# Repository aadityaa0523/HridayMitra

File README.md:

# HridayMitra: early warning of worsening heart failure at home

> **Monitoring, not diagnosis.** Research prototype for the Transfinitte 2026 hackathon (hardware track, problem statement by Dare 2 Dream Ventures).
> All patient data in this repository is **synthetic** (plus public PhysioNet BIDMC ECG for heart rate). No human data was collected.

**In one line:** a 90-second daily check-in on the patient's own chair, an amulet, and an offline alert engine that warns the family **days before** a heart-failure hospital visit (up to **4 days** in our worked example, median 3), for a build cost of about **₹4,400**.

**Jump to:** [The problem](#the-problem-and-the-idea) · [How it works](#how-it-works) · [Results](#results) · [Quick start](#quick-start) · [Saathi phone app](#saathi-phone-app) · [Hardware and firmware](#hardware-and-firmware) · [Simulate it](#simulate-it-no-hardware) · [Reproduce](#reproduce-everything) · [Repository map](#repository-map) · [Documents](#documents) · [Troubleshooting](#troubleshooting) · [Honest limits](#honest-limits)

---

## The problem and the idea

Fluid builds up silently for days before a heart-failure admission. A daily weight rule catches about one event in three and floods families with false alarms. Elders will not wear sticky patches, and rural homes have power cuts, 2G and low literacy.

HridayMitra measures what a weight scale cannot (fluid in the legs and chest) in the way an elder will actually accept (sit down, hands on a bar), learns each person's *own* normal, and tells the family **why** it raised an alert, by SMS, with no internet.

| Part | What it is | What it measures |
|---|---|---|
| **Check-in set** | A weighing platform under the patient's own chair (4 load cells, 4 stainless foot plates) plus a hand sensor bar (4 hand strips, fingertip optical cradle, ✓ / ✗ / SOS buttons, speaker, status light). No chair modification; never on wheeled chairs. | Weight; 8-electrode bioimpedance spectroscopy at 5 / 20 / 50 kHz (legs, arms, both sides → chest fluid by segmental subtraction; water outside the cells from a Cole-model fit, which cancels foot position and skin temperature); pulse and SpO₂; sit-to-stand speed from the platform's force; 3 spoken yes/no questions |
| **Kavach amulet** | ESP32-C3 + accelerometer on a breakaway cord, no magnets | Night breathing, night sit-ups, activity, a weekly 6-minute walk test (it finds the best 6 minutes itself, no button), falls, SOS |
| **Offline alert engine** | Runs on the ESP32 | Personal baseline, green / amber / red, reasons in plain words |
| **Care loop** | SMS over 2G with retries | family 1 → family 2 (30 min) → ASHA worker (2 h) → PHC doctor (6 h) |
| **Saathi app** | Offline PWA, 10 Indian languages | Elder, family, ASHA and doctor views |

## How it works

```mermaid
flowchart LR
  A[Kavach amulet<br/>ESP32-C3 + MPU6050] -- BLE advertisement, no pairing --> S
  S[Check-in set<br/>ESP32 + load cells + 8-electrode impedance + finger sensor<br/>offline alert engine] -- light + voice --> E[Elder]
  S -- SMS over 2G --> C[Care loop<br/>family 1 → family 2 → ASHA → PHC doctor]
  S -- BLE or USB --> P[Saathi phone app]
  S -- USB, optional --> D[Laptop bridge → live dashboard]
```

**The alert engine** (`engine/alert_engine.py`): each person's baseline is the median/MAD of their own days t−35..t−7. Only the worsening direction is scored. Red needs **two independent witnesses** (for example weight and leg fluid), and bad-data guards ignore guests on the platform, a toe ring bridging two plates, lifted feet and noisy fingers. The same engine exists three times and is held identical by tests:

| Where | File | Checked by |
|---|---|---|
| Python (research, dashboard) | `engine/alert_engine.py` | reference |
| C++ on the ESP32 | `firmware/hridaymitra_stool/engine_core.h` | `tests/test_engine_parity.py`: 100% of 3,231 days |
| TypeScript in the app | `app/src/engine/` | `app/tests/engine.test.ts` against `docs/app/engine_test_vectors.json` (2,732 comparisons) |

**Hybrid engine** (`engine/hybrid.py`): rules propose, a 13-weight logistic model trained on dev only must agree before red. It runs on the laptop and in the benchmark; the stool itself runs rules v3.

## Results

Synthetic cohorts; thresholds tuned on training patients, frozen, then tested once.

| | Rules engine v3 | Hybrid (rules + ML) | Weight rule (SCALE-HF) |
|---|---|---|---|
| Sensitivity, held-out patients | **66%** | **86%** | 40% |
| Sensitivity, external 1,000-patient cohort | **72%** | **86%** | 31% |
| Specificity (held-out) | 98.7% | 97.9% | 97.6% |
| False alerts per patient-month (held-out / external) | **0.06 / 0.06** | 0.19 / 0.09 | 0.53 / 0.38 |
| Median lead time before the visit | 3 days | 3 days | 2 days |

Full tables with 95% ranges and an open scorer anyone can run: [`benchmark/LEADERBOARD.md`](benchmark/LEADERBOARD.md), [`benchmark/README.md`](benchmark/README.md).

- **Calibrated to real trials.** The published FAST and SCALE-HF 1 weight rules score on our external cohort 20% / 33% caught and 4.8 / 4.85 unexplained alerts per year, against the published 23% / 35% and 4.3 / 4.18.
- **Robust.** It beats the weight rule in all 52 assumption-sensitivity scenarios and 14 of 15 stress cases. In the 15th (10% guest days) the rule catches more but fires about 30× more false alerts.
- **Care loop.** In simulation 92% of red alerts get a clinical review before the hospital visit, versus 27% with a single SMS.
- **Circuit.** LTspice puts every path within 0.05% of the exact answer. A Monte Carlo of 100 stools built from 5% parts keeps 99% of readings within 2%, and it found a real design bug (bias resistors 1 MΩ → 10 MΩ).
- **Heart rate on real ECG.** All 15 PhysioNet BIDMC CHF records: median error 0.15 bpm, 13 of 15 within 0.5 bpm. It fails on chf12, a very noisy recording.
- **Cost.** Parts list ₹3,917 (low) to ₹4,890 (plan price). Monte Carlo of price noise: median ₹4,402, 5th–95th percentile ₹4,319–4,486. Build cost only, no shipping.
- **Firmware.** The whole firmware runs through an emulated month: 26/26 claims pass and every light equals the Python engine.

Details: `reports/phase1_summary.md`, `reports/phase2_summary.md`, `sim/circuit/HOW_TO_VERIFY.md`, [`docs/EVIDENCE.md`](docs/EVIDENCE.md) (every problem-statement requirement → proof file, plus a failure-modes table).

## Quick start

Requires Python 3.11.

```bash
python run.py setup     # install packages, generate the synthetic cohorts if missing
python run.py test      # pytest suite, incl. the real firmware in an emulated month and C++ engine = Python engine
python run.py demo      # dashboard: patient light + voice, family SMS, ASHA/doctor trends, "break it" switches
```

| What you want | Command |
|---|---|
| Watch a pretend patient arrive live in the dashboard (no hardware) | `python run.py live --simulate P0022`, then `python run.py demo` → "Live stool" |
| Compile both boards (needs `arduino-cli` with the esp32 core) | `python run.py firmware` |
| Flash the stool (COM5) and the amulet (COM6) | `python run.py firmware --upload COM5 --amulet-port COM6` |
| Log the real stool's check-ins into the dashboard | `python run.py live --port COM5` |
| Prove the real stool decides exactly like the tested engine | `python run.py hil --port COM5` |
| Simulate the whole stool in Wokwi | `python run.py wokwi`, then `wokwi/README.md` |
| Re-run every result / rebuild every document | `python run.py reproduce` / `python run.py docs` |
| Everything | `python run.py all` |

In the dashboard, try patient **P0022**: slide to the red day, then tick "guest" and "toe ring" and watch the light refuse to lie.

## Saathi phone app

`app/` is **HridayMitra Saathi**: an offline-first PWA (React 18 + TypeScript + Vite, Tailwind, Workbox, Dexie) for one Android phone with role switching.

- **Elder mode:** big status orb, voice commands (offline Vosk packs), medicine reminders, a cancellable two-step emergency button that only opens the dialler.
- **Family:** trends, alerts, medicines, adherence, care contacts. **ASHA:** prioritised visit list, referral PDF and QR, weekly PHC summary. **Doctor:** timeline, care plan versions, labs, consult notes, sensitivity what-if.
- **Reports:** nine English/Hindi PDF formats, FHIR R4 JSON export, offline animated-QR transfer.
- **Device link:** BLE GATT or Web Serial to the stool (same JSON protocol as `firmware/hridaymitra_stool/app_link.h`), plus a built-in simulator.
- **Privacy:** records are encrypted at rest (AES-GCM, PBKDF2 PIN key). PINs are a demo mechanism, not production authentication.
- **Languages:** 10 UI languages (extra ones flagged "machine-translated, needs review"); light, dark and high-contrast themes; 48 pre-generated Hindi audio clips.
- **Verified:** 108 unit tests, 27 browser tests, mobile Lighthouse accessibility 100 (see `docs/app/PHASE_9.md`).

```bash
cd app
python ../tools/prepare_voice_models.py   # optional: 82 MB voice packs, not in git
npm ci && npm test && npm run dev
```

Node.js 22.12+. End-to-end tests: `npm run test:e2e` (Playwright, Pixel 5 viewport).

### Install it on a phone

A PWA installs only from **HTTPS or `localhost`**; plain `http://<lan-ip>` does not work.

**Option A: host it.** `cd app && npm ci && npm run build`, then upload `app/dist/` to the **root** of a static host (Netlify Drop, or Vercel / Cloudflare Pages with root directory `app`, build `npm run build`, output `dist`). The app uses root-absolute paths (`/models/`, `/audio/`), so it cannot sit under a sub-path such as GitHub Pages `/HridayMitra/`. On the phone: Android Chrome → menu → *Install app*; iPhone Safari → Share → *Add to Home Screen*.

**Option B: USB, no hosting (Android).** Enable *Developer options → USB debugging*, connect the phone, then:

```bash
cd app && npm ci && npm run build
npm run preview -- --port 4173          # serves the production build
adb reverse tcp:4173 tcp:4173           # in a second terminal
# phone: Chrome → http://localhost:4173 → menu → Install app
```

Open the installed app once while connected and wait for "App ready offline"; it then works without the cable. Web Bluetooth pairing needs Chrome on Android (not iOS). Per-phase details: `app/README.md`, `docs/app/PHASE_*.md`.

## Hardware and firmware

| Path | Contents |
|---|---|
| `firmware/hridaymitra_stool/` | ESP32 DevKit. 90 s check-in, HX711 weight (one HX711 for all four cells), 4 impedance paths with Goertzel, MAX30102 pulse/SpO₂, 3 questions, sit-to-stand fit, amulet scan, **the alert engine on the chip** (`engine_core.h`), SMS ladder with retries, replies and missed calls, engine state in flash, daily self-test, CHARGE / USE safety switch. Phone numbers and timings are in `config.h`. |
| `firmware/hridaymitra_amulet/` | ESP32-C3 + MPU6050. Night breathing, sit-ups, activity, 6-minute walk (`walk_core.h`), falls, SOS, sent in the BLE advertisement (no pairing). |
| `hardware/kicad/` | KiCad 9 schematic generated from code (ERC 0), netlist, PDF, and the Rev A PCB placement (`hridaymitra_pcb_unrouted.kicad_pcb`, Specctra `hridaymitra_pcb.dsn`). |
| `docs/hardware/` | HM-HW-001 block diagram, HM-HW-002 schematic set, HM-HW-003 power budget, HM-HW-004 PCB placement, system architecture, front-end sheet with LTspice test points. |
| `sim/circuit/` | LTspice netlists, Monte Carlo of 100 devices, mains-hum test, spectroscopy, self-calibration, IEC 60601-1 fault analysis, charger leakage. |

### PCB design (Rev A draft)

A 2-layer, 140 × 100 mm board for the custom part (8-electrode front end + ESP32), made by `tools/make_pcb.py` from the same netlist as the KiCad schematic: every part gets a footprint, parts are grouped by function (analog front end and electrode header top-left, ESP32 with its antenna at the top edge, module headers on the right, power and the CHARGE / USE switch bottom-left, buttons, LEDs and drivers bottom-right) and four M3 mounting holes. The script writes a Specctra DSN for autorouting (Freerouting) and, given the routed `.ses`, adds the tracks, pours ground on both layers and runs DRC.

Status: **placement only, routing next. Not fabricated, not yet reviewed by a layout engineer.**

```bash
python3 tools/make_pcb.py                       # needs KiCad 7+ (pcbnew Python module + footprint library)
java -jar freerouting-1.9.0.jar -de hardware/kicad/hridaymitra_pcb.dsn -do routed.ses
python3 tools/make_pcb.py routed.ses            # tracks + ground pour + DRC report
```

Safety design: two series coupling capacitors plus a current-limit resistor (every single fault within IEC 60601-1 type-BF limits, margin ≥ 12.8×), battery-only measuring, a CHARGE / USE switch that cuts both USB wires, impedance and ECG switchable off for pacemaker / ICD users.

Voice prompts: `python tools/make_voice_clips.py`. Recorded Hindi / Tamil WAVs in `firmware/voice/<lang>/` replace the built-in English voice.

## Simulate it (no hardware)

- **Wokwi** (`wokwi/`): the production firmware on an emulated ESP32 with a *virtual patient* chip (drag leg fluid, chest fluid, lifted foot, mains hum), a MAX30102 chip, a monitor chip showing the engine's decision, and a SIM800L chip with a phone screen that receives the SMS ladder. Build with `python run.py wokwi`; run in the browser in two minutes, see [`wokwi/README.md`](wokwi/README.md).
- **Software-in-the-loop** (`tests/test_firmware_sil.py`, `tests/sil/`): the same firmware compiled for the laptop and driven through a month.
- **Demo video:** [`docs/demo/hridaymitra_month_demo.mp4`](docs/demo/hridaymitra_month_demo.mp4), one month of the stool firmware driving the Wokwi screens.

## Reproduce everything

| Step | Command |
|---|---|
| Synthetic patients (PS cohort, 200 × 60 days) | `python sim/patients/make_patients.py` |
| Real-world cohort (1,000 × 180 days) | `python sim/patients/make_patients.py --patients 1000 --days 180 --event-fraction 0.1 --seed 43 --out data/processed/realworld` |
| Tune on training patients, freeze, test once | `python engine/leadtime_v2.py` |
| Stress tests and ablations | `python engine/stress_and_ablation.py` |
| Assumption sensitivity | `python engine/assumption_sensitivity.py` |
| Published-trial calibration | `python engine/calibrate_published.py` |
| ML comparator, hybrid engine, benchmark | `python engine/ml_comparator.py`, `python engine/hybrid.py`, `python benchmark/bench.py` |
| Score your own method | `python benchmark/score.py my_submission.csv test` |
| Care-loop simulator | `python sim/careloop/careloop.py` |
| Heart rate on PhysioNet BIDMC CHF | `python engine/validate_bidmc_hr.py` |
| LTspice: legs, chest paths, Monte Carlo, hum (needs LTspice) | `python sim/circuit/trunk_paths.py`, `montecarlo.py`, `hum.py` |
| KiCad schematic + ERC + netlist checks (needs KiCad 9) | `python tools/make_schematic.py` |
| Block diagram, cost simulation | `python tools/make_block_diagram.py`, `python tools/cost_sim.py` |

Every synthetic-patient parameter carries a source or is marked ASSUMPTION in [`data/processed/DATA.md`](data/processed/DATA.md); each ASSUMPTION was pushed low and high in the sensitivity sweep.

## Repository map

| Folder | What is inside |
|---|---|
| `engine/` | `signals.py` (raw → numbers), `alert_engine.py` (baseline, scores, lights, reasons), `hybrid.py`, `product.py` (sick-day plan, coaching, two users, FHIR), `sts.py` (sit-to-stand), `evaluate.py` (the four PS measures, no-peeking check), baselines, tuning scripts, frozen thresholds |
| `benchmark/` | Open benchmark v2: fixed splits with sha256, public scorer with bootstrap ranges, 5 baselines, leaderboard |
| `sim/patients/` | Synthetic patient generator |
| `sim/circuit/` | LTspice netlists and analyses |
| `sim/careloop/` | alert → family → ASHA → doctor simulator |
| `firmware/` | Stool (ESP32) and amulet (ESP32-C3) sketches |
| `hardware/kicad/` | Schematic, ERC report, netlist |
| `wokwi/` | Wokwi projects and custom chips |
| `app/` | Saathi PWA |
| `demo/` | Streamlit dashboard |
| `tools/` | Generators for documents, schematics, voice clips, Wokwi projects, stool bridge, cost simulation, `progress.py` |
| `tests/` | pytest suite plus C++ parity checks |
| `data/` | Synthetic cohorts and public BIDMC ECG |
| `reports/` | All results (CSV, PNG, summaries) |
| `docs/` | Report, pitch, build guide, wiring guide, evidence, decisions, app phase docs |
| `research_notes/` | Background research that shaped the design |
| `progress.json` | Workstream progress, rendered by `tools/progress.py` |

## Documents

- `docs/HridayMitra report.pdf` (2 pages) and `docs/HridayMitra pitch deck.pdf`, plus `docs/PITCH_SCRIPT.md`; regenerated from live results by `python run.py docs`.
- [`docs/EVIDENCE.md`](docs/EVIDENCE.md): requirement traceability, failure modes and safeguards, assumption ledger.
- [`docs/DECISIONS.md`](docs/DECISIONS.md): starting ideas, every design decision with evidence, next improvements.
- Build guide v3, wiring guide, physical build pack, user journey storyboard, block diagram: `docs/`.

## Troubleshooting

| Problem | Fix |
|---|---|
| Imports fail in `python run.py test` | Use Python 3.11, then `python run.py setup` |
| `npm run build` complains about missing `/models/*.bin` | `python tools/prepare_voice_models.py` (downloads and checks sha256) |
| "Install app" not offered on the phone | Not HTTPS / localhost, or first load unfinished; reload and wait for "App ready offline" |
| Phone cannot reach `localhost:4173` | Re-run `adb reverse tcp:4173 tcp:4173`; check `adb devices` lists the phone |
| No Bluetooth button in the app | Use Chrome on Android; iOS Safari has no Web Bluetooth |
| Firmware compile or upload fails | Install the `esp32` core for `arduino-cli`; check the COM port; hold BOOT while flashing if the board does not enter download mode |

## Honest limits

- **Synthetic data.** Patients are synthetic and calibrated to published weight-rule results. This shows the method works on the patterns we modelled; it is not clinical accuracy.
- **Lead time.** The 2–3 day lead is mostly set by how worsening is defined (3–10 days, speeding up at the end). The sweep shows this matters more than any hardware assumption.
- **Chest reading.** A weak signal: a +10% change stands out only after about a week of averaging, so it supports the leg and weight readings.
- **Untested on people.** The circuit is simulated with a textbook body model and not yet compared with a bench build. SpO₂ calibration is generic.
- **App.** Not installed or verified on a physical Android phone; draft translations and audio need human review; alarms need the app open; SMS from the app is a draft only.
- **Safety.** Never use on anyone with a pacemaker or ICD, and measure on battery only while a person touches the electrodes.

## License

[MIT](LICENSE). The medical-safety limits above still apply: this is a research prototype, not a medical device.

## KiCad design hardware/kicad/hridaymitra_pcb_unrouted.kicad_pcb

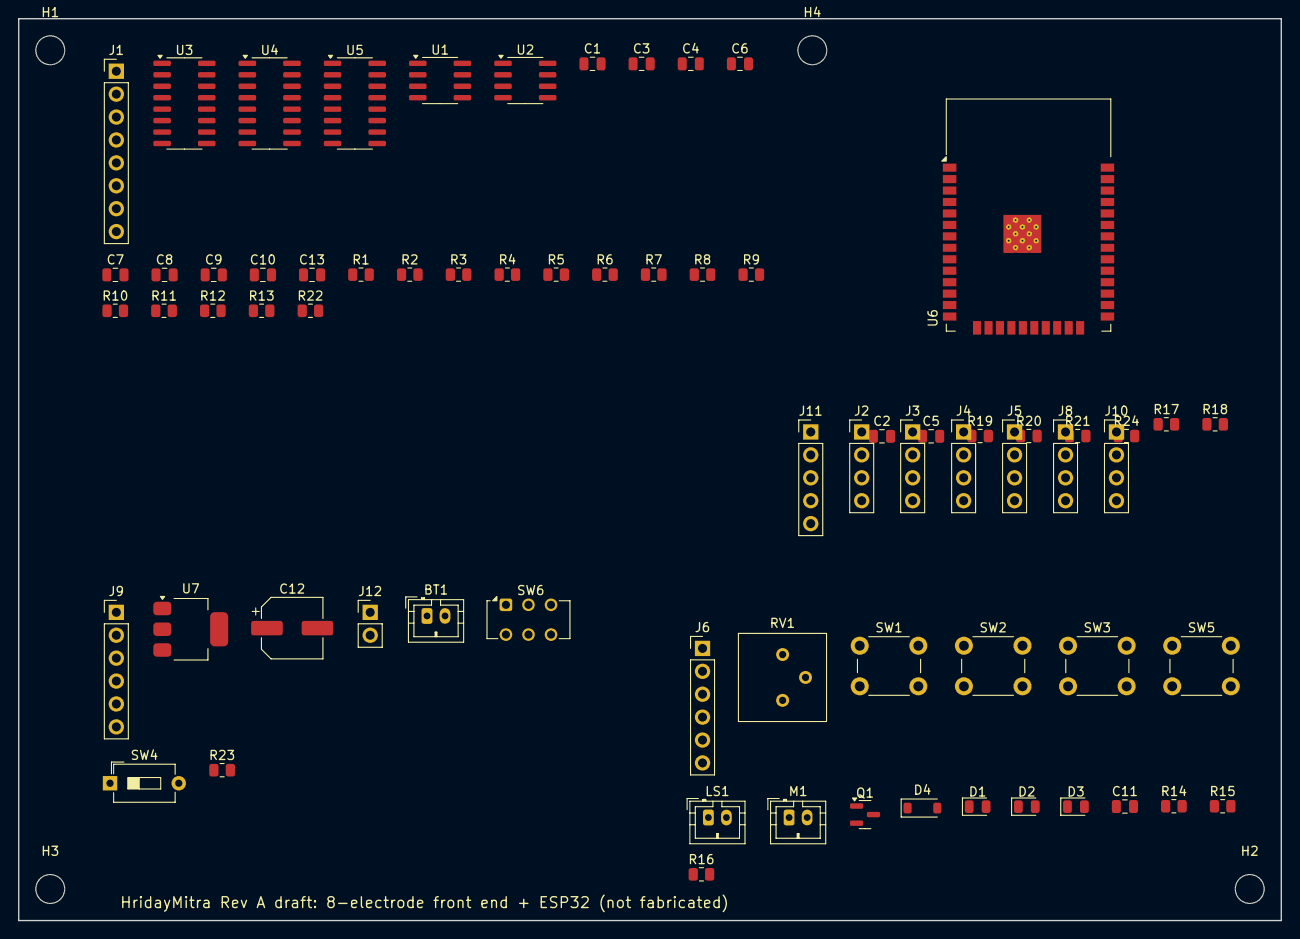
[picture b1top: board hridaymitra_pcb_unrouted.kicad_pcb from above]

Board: 2 copper layers, 140.0 x 100.0 mm, 74 parts (0 on the bottom side), 76 nets, no tracks yet.

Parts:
BT1: 18650 (protected); JST_PH_B2B-PH-K_1x02_P2.00mm_Vertical
C1, C10: 10u; C_0805_2012Metric
C2, C3, C4, C11: 1u; C_0805_2012Metric
C5: 10n; C_0805_2012Metric
C6, C7, C8, C9, C13: 100n; C_0805_2012Metric
C12: 1000u; CP_Elec_6.3x5.4
D1: green; LED_0805_2012Metric
D2: amber; LED_0805_2012Metric
D3: red; LED_0805_2012Metric
D4: 1N4148 flyback; D_SOD-123
H1, H2, H3, H4: MountingHole_3.2mm_M3
J1: Electrodes: 4 foot plate; PinHeader_1x08_P2.54mm_Vertical
J2: MAX30102 module (finger); PinHeader_1x04_P2.54mm_Vertical
J3: HX711 module: VCC GND DT; PinHeader_1x04_P2.54mm_Vertical
J4: HX711 module: E+ E- A- A; PinHeader_1x04_P2.54mm_Vertical
J5: 4 load cells as one brid; PinHeader_1x04_P2.54mm_Vertical
J6: PAM8403 module: 5V GND L; PinHeader_1x06_P2.54mm_Vertical
J8: SIM800L module: VCC GND; PinHeader_1x04_P2.54mm_Vertical
J9: TP4056 module: IN+ IN- B; PinHeader_1x06_P2.54mm_Vertical
J10: MT3608 module: IN+ IN- O; PinHeader_1x04_P2.54mm_Vertical
J11: AD8232 (optional; off fo; PinHeader_1x05_P2.54mm_Vertical
J12: USB-C charge socket (5V,; PinHeader_1x02_P2.54mm_Vertical
LS1: 4 ohm 3 W; JST_PH_B2B-PH-K_1x02_P2.00mm_Vertical
M1: coin vibration motor (se; JST_PH_B2B-PH-K_1x02_P2.00mm_Vertical
Q1: 2N2222 (vibration driver; SOT-23
R1, R2: 10k 1%; R_0805_2012Metric
R3, R23, R24: 100k; R_0805_2012Metric
R4: 4.7k 1%; R_0805_2012Metric
R5: 120; R_0805_2012Metric
R6, R7, R12, R13, R17, R21: 1k; R_0805_2012Metric
R8, R9: 10M; R_0805_2012Metric
R10: 16k (15k+1k); R_0805_2012Metric
R11: 1.5k; R_0805_2012Metric
R14, R15, R16: 220; R_0805_2012Metric
R18: 2.2k; R_0805_2012Metric
R19: 10k (on DevKit); R_0805_2012Metric
R20: 10k; R_0805_2012Metric
R22: 100 0.1% (Rcal); R_0805_2012Metric
RV1: 10k volume; Potentiometer_Bourns_3386P_Vertical
SW1: green button; SW_PUSH_6mm
SW2: red button; SW_PUSH_6mm
SW3: SOS button; SW_PUSH_6mm
SW4: power switch; SW_DIP_SPSTx01_Slide_6.7x4.1mm_W7.62mm_P2.54mm_LowProfile
SW5: tablet-drawer microswitc; SW_PUSH_6mm
SW6: CHARGE / USE slide switc; SW_CK_JS202011CQN_DPDT_Straight
U1: MCP6002; SOIC-8_3.9x4.9mm_P1.27mm
U2: INA126; SOIC-8_3.9x4.9mm_P1.27mm
U3: 74HC4053 (body / referen; SOIC-16_3.9x9.9mm_P1.27mm
U4: 74HC4052 (current pair); SOIC-16_3.9x9.9mm_P1.27mm
U5: 74HC4052 (sense pair); SOIC-16_3.9x9.9mm_P1.27mm
U6: ESP32-WROOM-32 (DevKit); ESP32-WROOM-32
U7: 3.3 V LDO (on DevKit); SOT-223-3_TabPin2

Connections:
/+3V3: C6.1, C7.1, C8.1, C9.1, C10.1, C13.1, J2.1, J3.1, J11.1, R1.1, R19.1, R20.1, U1.8, U2.7, U3.16, U4.16, U5.16, U6.2, U7.2
/+5V: D4.1, J6.1, J10.3, M1.1, U7.3
/AMP_IN: J6.3, RV1.2
/BAT_P: BT1.1, J9.3
/BTN_G: SW1.1, U6.26
/BTN_R: SW2.1, U6.29
/BTN_SOS: SW3.1, U6.23
/CAL_SEL: U3.9, U6.14
/CHG_IN: J9.1, R23.1, SW6.2
/CHG_SENSE: R23.2, R24.1, U6.5
/DAC_EXC: C2.1, U6.10
/DRAWER: R20.2, SW5.1, U6.4
/ECG_OUT: J11.3, U6.6
/EN: R19.2, U6.3
/EXC_IN: C2.2, R3.1, U1.5
/EXC_OUT: C3.1, U1.6, U1.7
/GND: BT1.2, C1.2, C5.2, C6.2, C7.2, C8.2, C9.2, C10.2, C12.2, C13.2, J2.2, J3.2, J6.2, J6.4, J8.2, J9.2, J9.4, J9.6, J10.2, J10.4, J11.2, Q1.2, R2.2, R14.2, R15.2, R16.2, R18.2, R24.2, RV1.3, SW1.2, SW2.2, SW3.2, SW5.2, SW6.5, U1.4, U2.4, U3.6, U3.7, U3.8, U4.6, U4.7, U4.8, U5.6, U5.7, U5.8, U6.1, U6.15, U6.38, U6.39, U7.1
/GSM_RX: J8.3, U6.27
/GSM_RXD: J8.4, R17.2, R18.1
/GSM_TX: R17.1, U6.28
/HX_DT: J3.3, U6.8
/HX_SCK: J3.4, U6.13
/INA_N: U2.2, U3.15
/INA_OUT: R11.1, U2.6
/INA_P: U2.3, U3.14
/I_SNK: C4.1, U4.3
/I_SRC: R4.2, U4.13
/LC_AN: J4.3, J5.3
/LC_AP: J4.4, J5.4
/LC_EN: J4.2, J5.2
/LC_EP: J4.1, J5.1
/LED_A: D2.2, U6.37
/LED_A_K: D2.1, R15.1
/LED_G: D1.2, U6.16
/LED_G_K: D1.1, R14.1
/LED_R: D3.2, U6.24
/LED_R_K: D3.1, R16.1
/LF_FORE: J1.1, U4.4, U4.12
/LF_HEEL: R6.2, U5.4, U5.12
/LF_HEEL_E: J1.2, R6.1
/LH_IN: R12.2, U5.11, U5.14
/LH_IN_E: J1.6, R12.1
/LH_OUT: J1.5, U4.11, U4.14
/N1: C3.2, R4.1
/NCAL: R5.2, R22.1, U3.3
/PATH_S0: U4.10, U5.10, U6.9
/PATH_S1: U4.9, U5.9, U6.12
/RET: C4.2, R5.1, U3.5
/RF_FORE: J1.3, U4.1, U4.2
/RF_HEEL: R7.2, U5.1, U5.2
/RF_HEEL_E: J1.4, R7.1
/RG1: R10.1, U2.1
/RG2: R10.2, U2.8
/RH_IN: R13.2, U5.5, U5.15
/RH_IN_E: J1.8, R13.1
/RH_OUT: J1.7, U4.5, U4.15
/RTAP: U3.4, U3.13
/SA: R8.1, U3.12, U5.13
/SB: R9.1, U3.2, U5.3
/SCL: J2.3, U6.36
/SDA: J2.4, U6.33
/SEL: U3.10, U3.11, U6.30
/SPK_N: J6.6, LS1.2
/SPK_P: J6.5, LS1.1
/USB_5V: J12.1, SW6.1
/USB_GND: J12.2, SW6.4
/VBAT: C12.1, J8.1, J10.1, SW4.2
/VBAT_RAW: J9.5, SW4.1
/VIBRA: R21.1, U6.31
/VIB_B: Q1.1, R21.2
/VIB_C: D4.2, M1.2, Q1.3
/VOICE_AC: C11.2, RV1.1
/VOICE_DAC: C11.1, U6.11
/VREF: R3.2, R8.2, R9.2, R22.2, U1.1, U1.2, U2.5, U3.1
/VREF_IN: C1.1, R1.2, R2.1, U1.3
/Z_ADC: C5.1, R11.2, U6.7

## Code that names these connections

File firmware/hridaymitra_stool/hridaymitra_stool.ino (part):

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#include "app_link.h"                                   // BLE GATT + USB link to the HridayMitra Saathi app

// ---- pins (build guide v3.1) ----
const int HX_DT = 32, HX_SCK = 14, VOICE = 26, Z_ADC = 35, SEL = 18, PATH_S0 = 33, PATH_S1 = 27;
const int LED_G = 13, LED_A = 23, LED_R = 2, BTN_G = 4, BTN_R = 5, BTN_SOS = 15, GSM_RX = 16, GSM_TX = 17;
const int VIBRA = 19, DRAWER = 36;                       // seat vibration motor (via NPN); tablet-drawer switch to GND
const int CHG_SENSE = 39;                                // high = CHARGE/USE switch on CHARGE (charger connected): never measure
const int CAL_SEL = 12;                                  // 74HC4053 switch C: high = reference across Rcal only, low = across R5 + Rcal
const float RCAL = 100.0f;                               // 0.1 % precision reference (self-calibrating front end)
const float REF_RATIO = 2.2f, REF_TOL = 0.09f;          // (R5 120 + Rcal 100) / Rcal; outside 2.0-2.4 = fault (sim/circuit/selfcal.py)
float lastRefRatio = NAN;
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  say(CLIP_Q_BREATH); int a = button(20000); d.breathless = a < 0 ? NAN : a;
  say(CLIP_Q_PILLOW); a = button(20000); d.orthopnea = a < 0 ? NAN : a;
  int took = -1;
  if (drawerToday) took = 1;                             // tablet drawer opened today: no need to ask
  else { say(CLIP_Q_TABLETS); a = button(20000); took = a < 0 ? -1 : (a == 1 ? 1 : 0); }
  say(CLIP_STAND);
  uint32_t t0 = millis();
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void setup() {
  Serial.begin(115200);
  Serial2.begin(9600, SERIAL_8N1, GSM_RX, GSM_TX);
  for (int p : {LED_G, LED_A, LED_R, SEL, PATH_S0, PATH_S1, HX_SCK, VIBRA, CAL_SEL}) pinMode(p, OUTPUT);   // GPIO12 is a boot pin: only a high-impedance select input on it
  for (int p : {BTN_G, BTN_R, BTN_SOS}) pinMode(p, INPUT_PULLUP);
  pinMode(HX_DT, INPUT); pinMode(DRAWER, INPUT); pinMode(CHG_SENSE, INPUT);         // GPIO36 has no internal pull-up: 10 k to 3.3 V on the board
  analogReadResolution(12);
  Wire.begin(21, 22); maxInit();
  excCfg.chan_id = DAC_CHAN_0; excCfg.freq_hz = 5000; excCfg.clk_src = DAC_COSINE_CLK_SRC_DEFAULT;
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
